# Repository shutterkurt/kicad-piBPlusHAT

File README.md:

kicad-piBPlusHAT
================

A KiCad template for raspberri pi b+ HAT

work in progress

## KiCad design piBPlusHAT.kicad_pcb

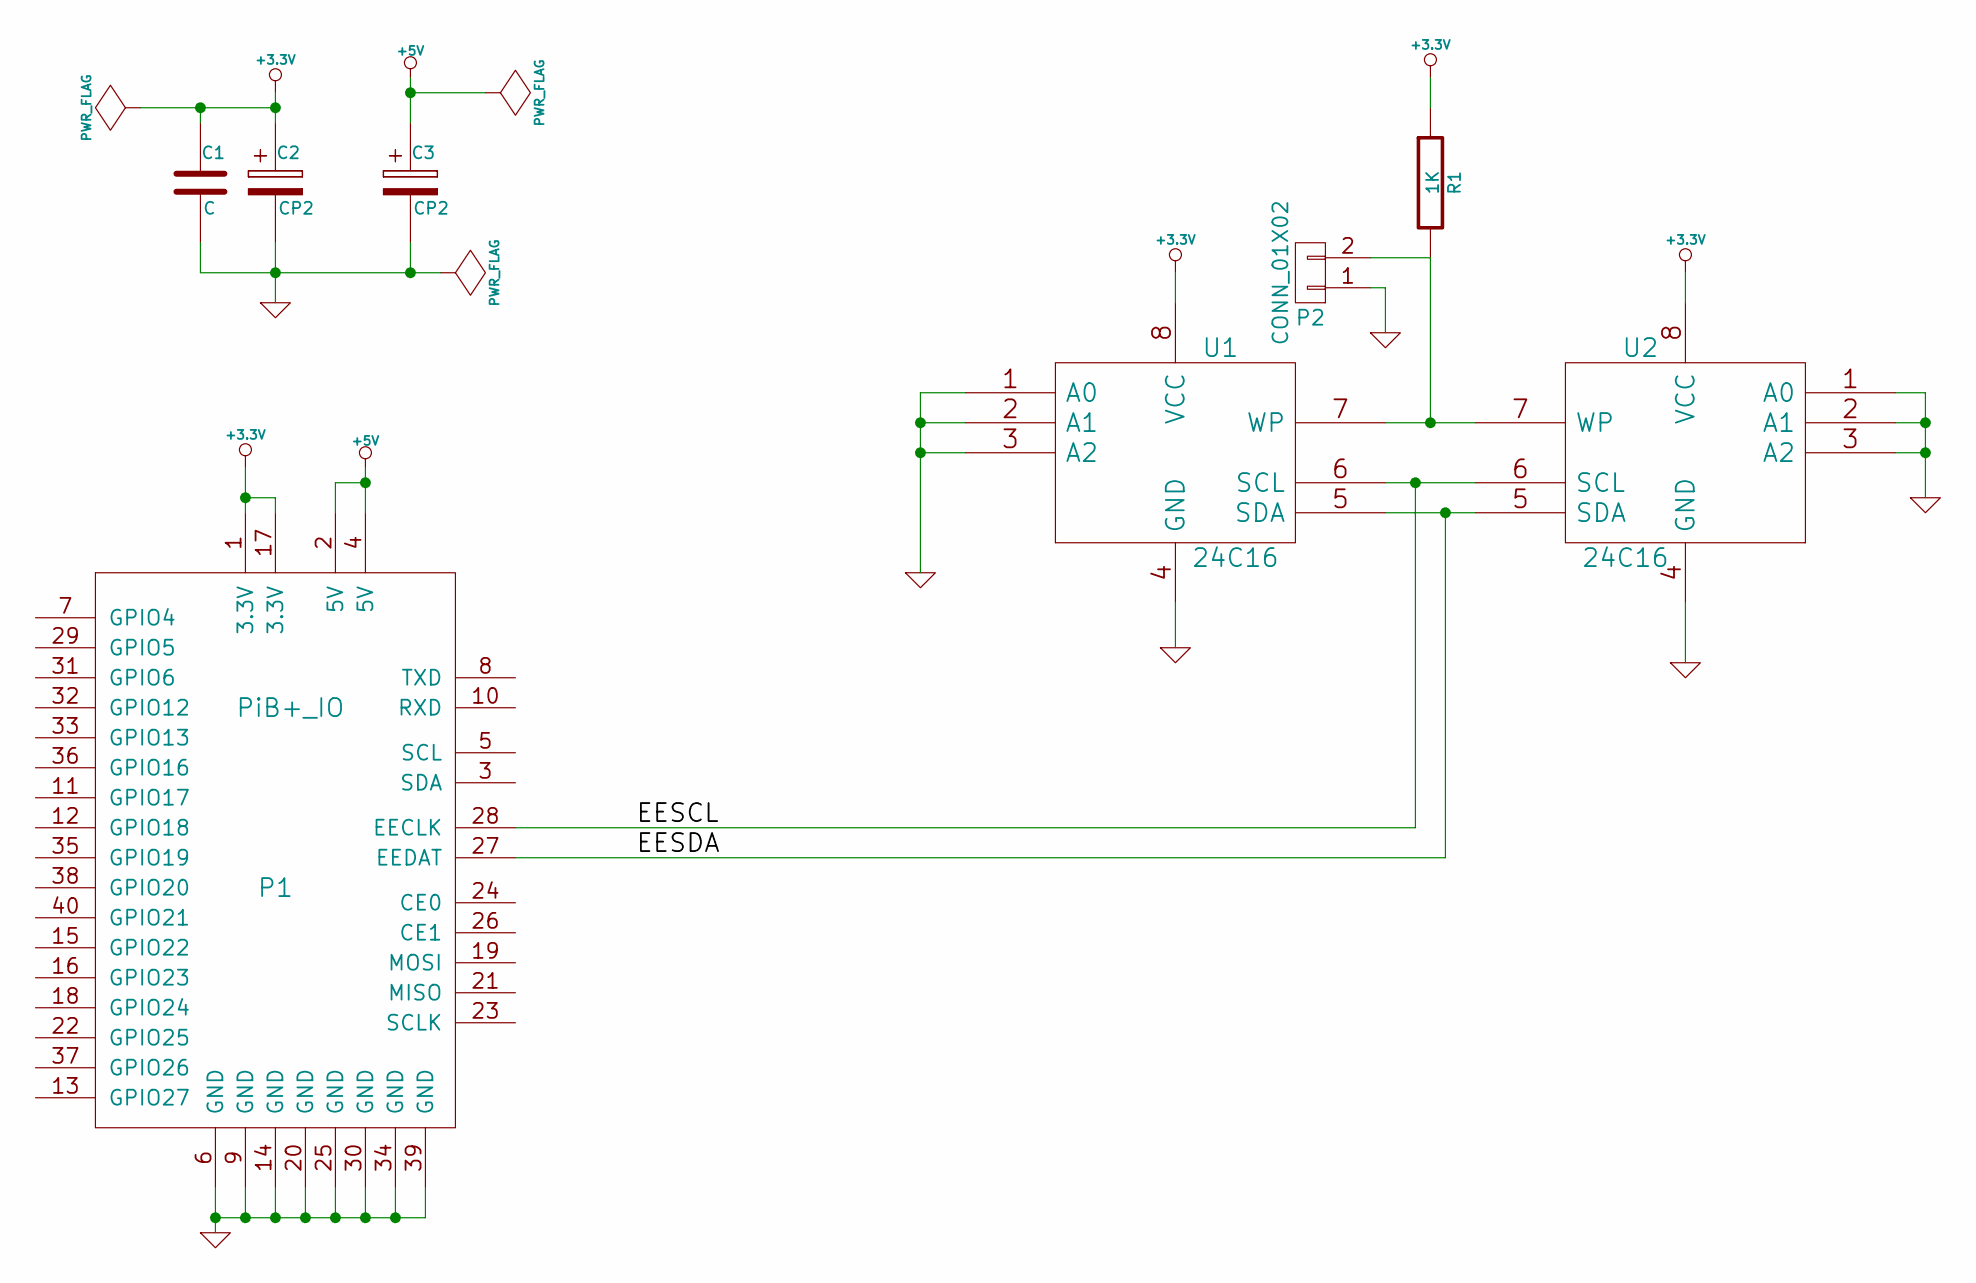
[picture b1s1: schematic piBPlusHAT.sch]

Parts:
C1: C; C1
C2, C3: CP2; Capacitor5x11RM2.5
P1: PiB+_IO; Socket_Strip_Straight_2x20
P2: CONN_01X02; Pin_Header_Straight_1x02
R1: 1K; R4
U1: 24C16; PDIP-8
U2: 24C16; SOIC-8-N

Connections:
+3.3V: C1.1, C2.1, P1.1 (3.3V), P1.17 (3.3V), R1.1, U1.8 (VCC), U2.8 (VCC)
+5V: C3.1, P1.2 (5V), P1.4 (5V)
/EESCL: P1.28 (EECLK), U1.6 (SCL), U2.6 (SCL)
/EESDA: P1.27 (EEDAT), U1.5 (SDA), U2.5 (SDA)
GND: C1.2, C2.2, C3.2, P1.6 (GND), P1.9 (GND), P1.14 (GND), P1.20 (GND), P1.25 (GND), P1.30 (GND), P1.34 (GND), P1.39 (GND), P2.1, U1.1 (A0), U1.2 (A1), U1.3 (A2), U1.4 (GND), U2.1 (A0), U2.2 (A1), U2.3 (A2), U2.4 (GND)
unnamed: P2.2, R1.2, U1.7 (WP), U2.7 (WP)

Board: 2 copper layers, 8 parts (1 on the bottom side), 6 nets, no tracks yet.

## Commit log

2014-12-20 initial
